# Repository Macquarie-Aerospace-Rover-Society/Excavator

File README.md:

# Excavator ROS 2 Humble Project

ROS 2 Humble workspace for the MARS (Macquarie University Rover Society) front loader bucket subsystem, officially nicknamed **Excavator**, for the Australian Rover Challenge.

This project implements the kinematics and static force model from the provided MATLAB simulator and publishes state suitable for controller integration and RViz visualization.

## Workspace Layout

- `src/excavator_kinematics`: ROS 2 Python package with the model, node, launch, and config.

## Features

- Elevation (`re`) and tilt (`rt`) command handling.
- Actuator stroke clamping to hardware limits (380-630 mm).
- Joint coordinate calculation for `J1`, `J2`, `J3`, `J4`.
- Stroke percentages and end-stop warning flags.
- Angular speed estimation from actuator stroke speed.
- Static force estimation (`F_L1`, `F_L2`) under payload gravity.
- ROS publishers for joint state, telemetry, and RViz markers.

## Node Architecture

The project is split into multiple ROS nodes:

- `excavator_state_node`: computes mechanism state from desired command angles.
- `excavator_visualization_node`: publishes `/joint_states`, markers, and telemetry from computed state.
- `excavator_keyboard_node`: optional keyboard teleop for desired `re` / `rt` / `mass`.

## Build

From the workspace root (`Excavator`):

```bash
source /opt/ros/humble/setup.bash
colcon build
source install/setup.bash
```

## Gazebo Prerequisite (Ubuntu-22.04 / ROS 2 Humble)

Install modern Gazebo Sim (`gz sim`) support:

```bash
sudo apt update
sudo apt install ros-humble-ros-gz-sim ros-humble-ros-gz-bridge
```

If `ros-humble-ros-gz-sim` is unavailable in your apt sources, install:

```bash
sudo apt install ros-humble-ros-gz ros-humble-ros-gz-bridge
```

## Run

Single supported launch path (Modern Gazebo GUI fallback + keyboard teleop):

```bash
ros2 launch excavator_kinematics excavator_gz_sim_gui.launch.py enable_keyboard:=true
```

VS Code task:

- `Launch Excavator`

Keyboard controls in teleop node:

- `w/s`: increase/decrease elevation `re`
- `a/d`: increase/decrease tilt `rt`
- `r/f`: increase/decrease load mass
- `z`: reset to initial setpoints
- `q`: quit keyboard node

## Command Topic

Publish command inputs to:

- Topic: `excavator/command`
- Type: `geometry_msgs/msg/Vector3`
- Fields:
- `x`: elevation angle `re` in degrees
- `y`: tilt angle `rt` in degrees
- `z`: payload mass in kg

Angle convention:

- `re` and `rt` follow the MATLAB world-frame definitions in the layout diagram.
- The URDF bucket joint is relative, so the node publishes `excavator_bucket_joint = rt - re` internally.

Example:

```bash
ros2 topic pub /excavator/command geometry_msgs/msg/Vector3 "{x: 30.0, y: -45.0, z: 10.0}" --once
```

## Published Topics

- `/joint_states` (`sensor_msgs/msg/JointState`)
- `/excavator/stroke_monitor` (`std_msgs/msg/Float32MultiArray`)
- `/excavator/forces` (`geometry_msgs/msg/Vector3`)
- `/excavator/markers` (`visualization_msgs/msg/MarkerArray`)

`/excavator/stroke_monitor` array order:

1. `L1_mm`
2. `L2_mm`
3. `L1_pct`
4. `L2_pct`
5. `re_dot`
6. `rt_dot`

## Notes

- Geometry is computed in millimeters to match the original mechanism model.
- RViz markers are converted to meters (`mm * 0.001`) for visualization.
- Dynamics are static/quasi-static estimates (no full multibody dynamics yet).

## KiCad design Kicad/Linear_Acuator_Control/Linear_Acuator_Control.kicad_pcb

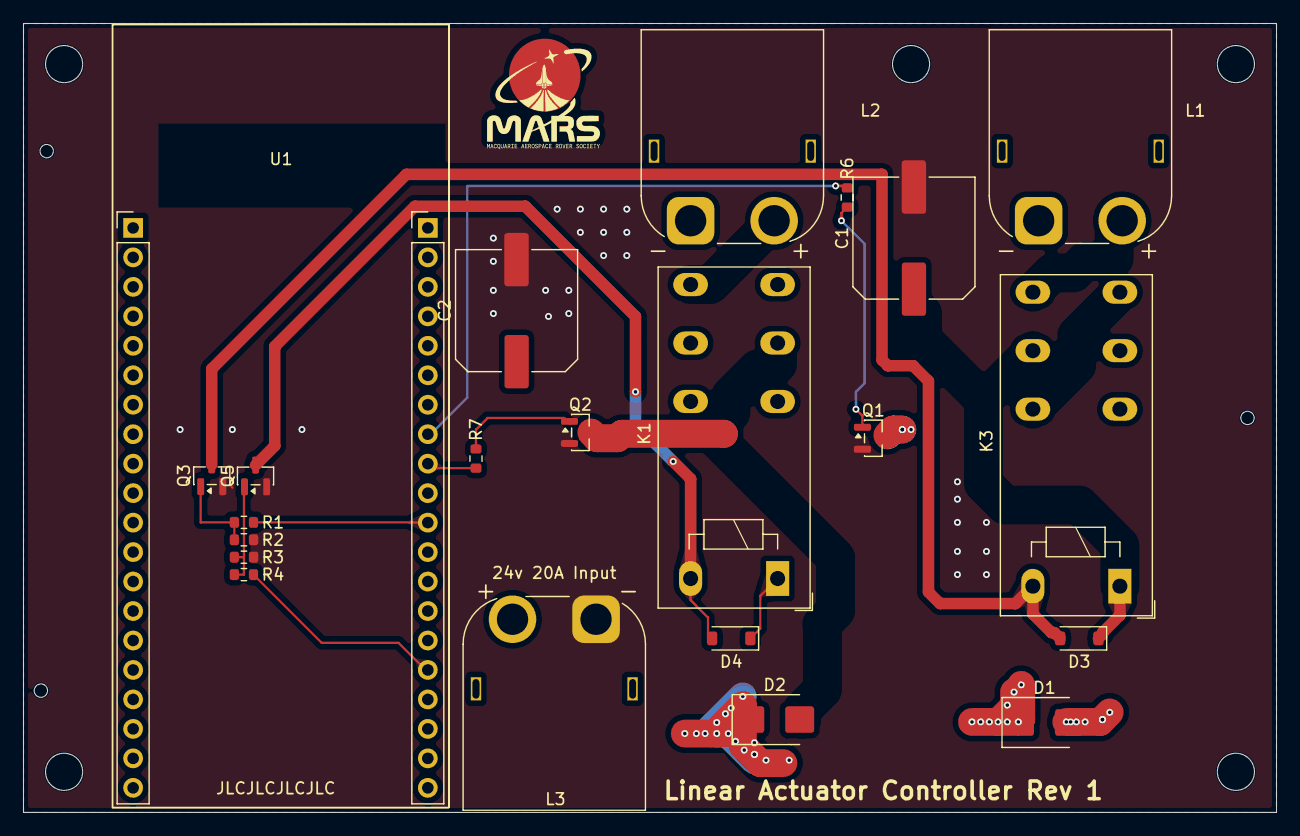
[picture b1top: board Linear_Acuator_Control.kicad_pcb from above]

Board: 2 copper layers, 108.0 x 68.0 mm, 22 parts (0 on the bottom side), 18 nets.

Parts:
C1, C2: C_Elec_10x10.2
D1, D2: D_SMB
D3, D4: 1N4148W; D_SOD-123
K1, K3: RT42xAxx; Relay_DPDT_Schrack-RT2-FormC_RM5mm
L1: Linear actuator 1; AMASS_XT60PW-M_1x02_P7.20mm_Horizontal
L2: Linear Actuator 2; AMASS_XT60PW-M_1x02_P7.20mm_Horizontal
L3: 24v 20A Input; AMASS_XT60PW-M_1x02_P7.20mm_Horizontal
Q1, Q2: SOT-23
Q3, Q5: 2N7002; SOT-23
R1, R4: 1k; R_0603_1608Metric
R2, R3: 10k; R_0603_1608Metric
R6, R7: 220; R_0603_1608Metric
U1: ESP32-S3-WROOM; ESP32-S3-WROOM-Cam

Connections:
+24V: D1.1, D2.1, D3.1, D4.1, K1.21, K1.A1, K3.21, K3.A1, L3.2
Dir L1: R1.2, U1.36 (GPIO39/MTCK)
Dir L2: R4.2, U1.47
GND: C1.2, C2.2, L3.1, Q1.2, Q2.2, Q3.2 (S), Q5.2 (S), R2.2, R3.2
L1SwitchedLow: D1.2, K3.11, Q1.3
unnamed: D2.2, K1.11, Q2.3
unnamed: D3.2, K3.A2, Q3.3 (D)
unnamed: D4.2, K1.A2, Q5.3 (D)
unnamed: K3.14, K3.22, L1.1
unnamed: K3.12, K3.24, L1.2
unnamed: K1.14, K1.22, L2.1
unnamed: K1.12, K1.24, L2.2
unnamed: Q1.1, R6.1
unnamed: Q3.1 (G), R1.1, R2.1
unnamed: Q5.1 (G), R3.1, R4.1
unnamed: U1.1 (3V3), U1.2 (3V3)
Speed L1: R6.2, U1.39 (GPIO42/MTMS)
Speed L2: R7.1, U1.38 (GPIO41/MTDI)

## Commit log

2026-03-23 Initial commit: Excavator ROS2 project
2026-03-26 Electrical
2026-03-28 commit updated schematic
    shifted to solid state control for motor speed, with relays for direction, need to discuss relay selection to ensure adequate current carrying capacity.
2026-03-28 flyback diode for protections
2026-03-29 Modified schematic for ESP32 integration and routed PCB
2026-03-30 Changed footprint for correct ESP32 Module
2026-03-31 adding esp32 step file to check for interference
2026-03-31 Rerouting dodgy traces, fixing ESP32 footprint
2026-04-01 Changed Mosfets to better suit 3.3v logic levels
2026-04-07 finished routing with updated design
2026-04-08 added MARS logo to front
2026-04-09 small stuff
2026-04-20 v1.3 For 5v logic
2026-04-22 Updated to SMD comp
2026-04-25 Final changes before production
    Changed some comps and added TVS diodes for overvoltage protection.
2026-04-29 component changes
2026-05-01 rearranging tracks for solder busses
2026-05-03 adding part numbers
    for some reason the diodes dont work properly with lcsc idk will investigate
2026-05-04 removing solder mask over current carrying traces, cleaning up other stuff
2026-05-15 Fab Ready
    Im pretty sure
